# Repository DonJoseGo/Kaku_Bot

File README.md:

# Kaku_Bot
Robot con movimiento autónomo y un brazo de movimiento repetitivo

# Integrantes
* Jose Gómez
* Jose Miguel
* Johan Navarro
# Descripción
  Carrito con diferentes rostros cambiables realizado con madera capaz de sortear obstaculos y deplazarse en superficies planas. Cuenta con un ultrasonido que detecta estructuras cercanas y según la desicion del usuario el robot puede realizar una acción como prender una luz led del color que escoja. Finalmente su brazo con movimiento oscilatorio puede ser usado para mover objetos pequeños.
# Objetivos
Diseñar un robot economico que sea fácilmente programable para fomentar conceptos básicos en programación.
## Objetivos epecíficos 
* Trabajar con microcontroladores diferentes a los convencionales como el arduino.
* Elaborar un código base en JavaScrypt y LUA que permita su fácil replicación en la aplicación catalejo, la cual permite al usuario programar fácimente desde celular con bloques de comandos.
* Generar un diseño atractivo que llame la atención del público y despierte el interés de los usuarios en la elaboración de proyectos de este estilo.
# Alcance
El robot tiene un costo economico y puede ser replicado fácilmente con ayuda de los elementos mencionados en este proyecto.
# Resultados
El robot tiene buen movimiento gracias a los 5 voltios que recibe de la tarjeta. Adicional a ellos se mueve en todas las direcciones y es programable muy fácilmente con ayuda de la aplicación Catalejo. En el siguiente video se puede observar el movimiento que realiza el robot y los bloques de código usados de forma muy sencilla. Los siguientes videos evidencian la sencilla programación que requiere para funcionar adecuadamente.

https://github.com/DonJoseGo/Kaku_Bot/assets/133617253/81911118-b9c0-4a47-818a-cdb0a08687de

En el siguiente video podemos ver como el robot avanza (no uniformemente como ya habíamos dicho) y se detiene al detectar el obtaculo cercano, al final el robot se cae pero esto es debido al peso de la Power band que lleva en su cabeza.

https://github.com/DonJoseGo/Kaku_Bot/assets/133617253/b0575f9b-56e6-4335-94fb-eddb37d2c51a

#Conclusiones
En los videos se puede ver como es la programación del robot de forma sencilla, esto cumple nuestro objetivo general, debido a que genera interes en programación para los usuarios del robot.

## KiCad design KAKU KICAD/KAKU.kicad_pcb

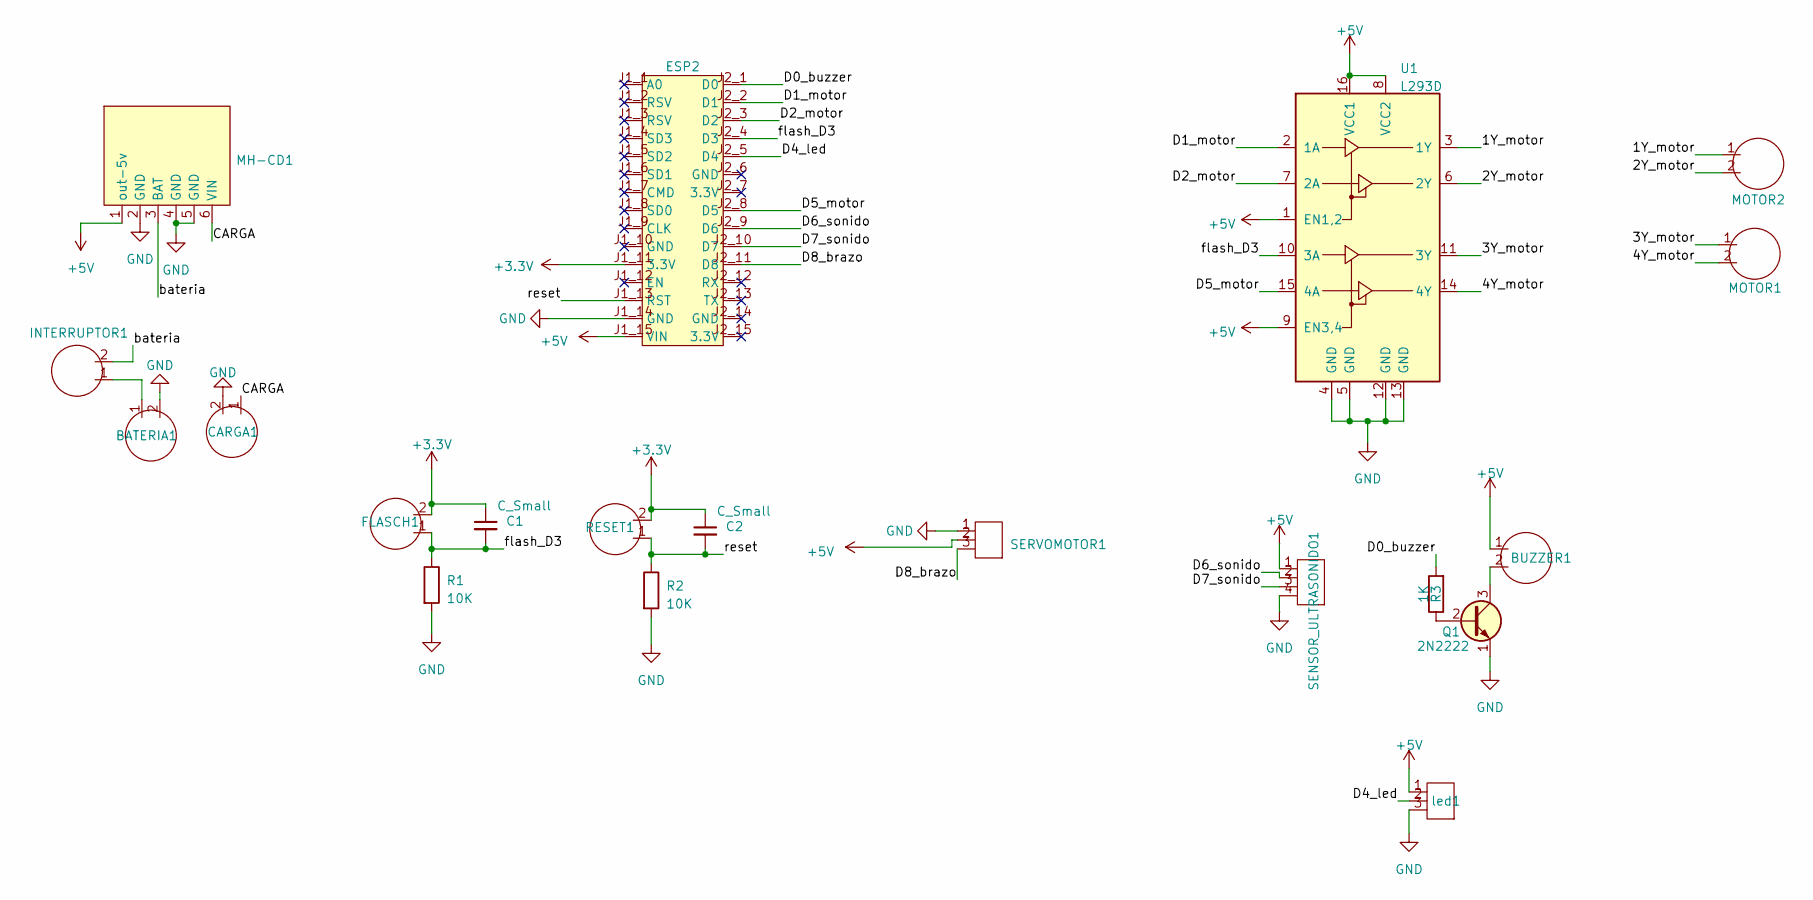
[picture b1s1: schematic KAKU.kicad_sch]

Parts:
BATERIA1: 2P
BUZZER1: 2P
C1, C2: C_Small; CP_Radial_D4.0mm_P1.50mm
CARGA1: 2P
ESP2: SEEED_113990105
FLASCH1: 2P
INTERRUPTOR1: 2P
MH-CD1: MH-CD42
MOTOR1, MOTOR2: 2P
Q1: 2N2222
R1, R2: 10K; R
R3: 1K; R
RESET1: 2P
SENSOR_ULTRASONIDO1: 4P
SERVOMOTOR1: 3P
U1: L293D; DIP-16_W7.62mm
led1: 3P

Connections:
+3.3V: C1.1, C2.1, ESP2.J1_11 (3.3V), FLASCH1.2, RESET1.2
+5V: BUZZER1.1, ESP2.J1_15 (VIN), MH-CD1.1 (out-5v), SENSOR_ULTRASONIDO1.1, SERVOMOTOR1.2, U1.1 (EN1,2), U1.8 (VCC2), U1.9 (EN3,4), U1.16 (VCC1), led1.1
/1Y_motor: MOTOR2.1, U1.3 (1Y)
/2Y_motor: MOTOR2.2, U1.6 (2Y)
/3Y_motor: MOTOR1.1, U1.11 (3Y)
/4Y_motor: MOTOR1.2, U1.14 (4Y)
/CARGA: CARGA1.1, MH-CD1.6 (VIN)
/D0_buzzer: ESP2.J2_1 (D0), R3.2
/D1_motor: ESP2.J2_2 (D1), U1.2 (1A)
/D2_motor: ESP2.J2_3 (D2), U1.7 (2A)
/D4_led: ESP2.J2_5 (D4), led1.2
/D5_motor: ESP2.J2_8 (D5), U1.15 (4A)
/D6_sonido: ESP2.J2_9 (D6), SENSOR_ULTRASONIDO1.2
/D7_sonido: ESP2.J2_10 (D7), SENSOR_ULTRASONIDO1.3
/D8_brazo: ESP2.J2_11 (D8), SERVOMOTOR1.3
/bateria: INTERRUPTOR1.2, MH-CD1.3 (BAT)
/flash_D3: C1.2, ESP2.J2_4 (D3), FLASCH1.1, R1.1, U1.10 (3A)
/reset: C2.2, ESP2.J1_13 (RST), R2.1, RESET1.1
GND: BATERIA1.2, CARGA1.2, ESP2.J1_14 (GND), MH-CD1.2 (GND), MH-CD1.4 (GND), MH-CD1.5 (GND), Q1.1 (E), R1.2, R2.2, SENSOR_ULTRASONIDO1.4, SERVOMOTOR1.1, U1.4 (GND), U1.5 (GND), U1.12 (GND), U1.13 (GND), led1.3
unnamed: BATERIA1.1, INTERRUPTOR1.1
unnamed: Q1.2 (B), R3.1
unnamed: BUZZER1.2, Q1.3 (C)

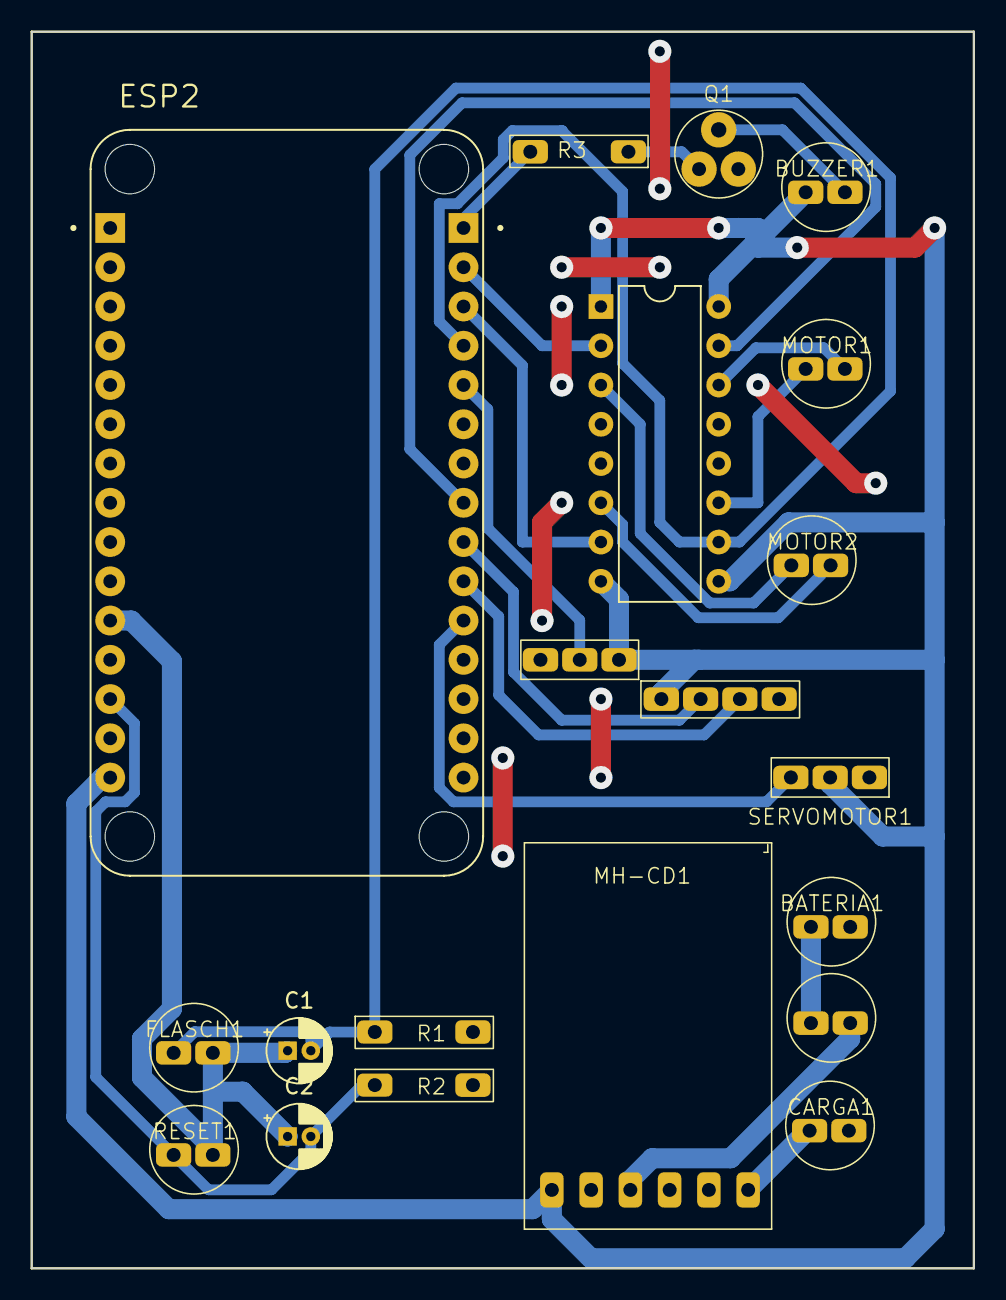
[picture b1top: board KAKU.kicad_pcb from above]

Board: 2 copper layers, 61.0 x 80.0 mm, 20 parts (0 on the bottom side), 22 nets.

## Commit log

2023-06-25 README.md
2023-06-28 Funcionamiento del robot
    En los videos se puede ver como es la programación del robot de forma sencilla, esto cumple nuestro objetivo general, debido a que genera interes en programación para los usuarios del robot.
    En el primer video, el robot tiene buen movimiento gracias a los 5 voltios que recibe de la tarjeta. Adicional a ellos se mueve en todas las direcciones y es programable muy fácilmente con ayuda de l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
    En el segundo video podemos ver como el robot avanza (no uniformemente como ya habíamos dicho) y se detiene al detectar e
